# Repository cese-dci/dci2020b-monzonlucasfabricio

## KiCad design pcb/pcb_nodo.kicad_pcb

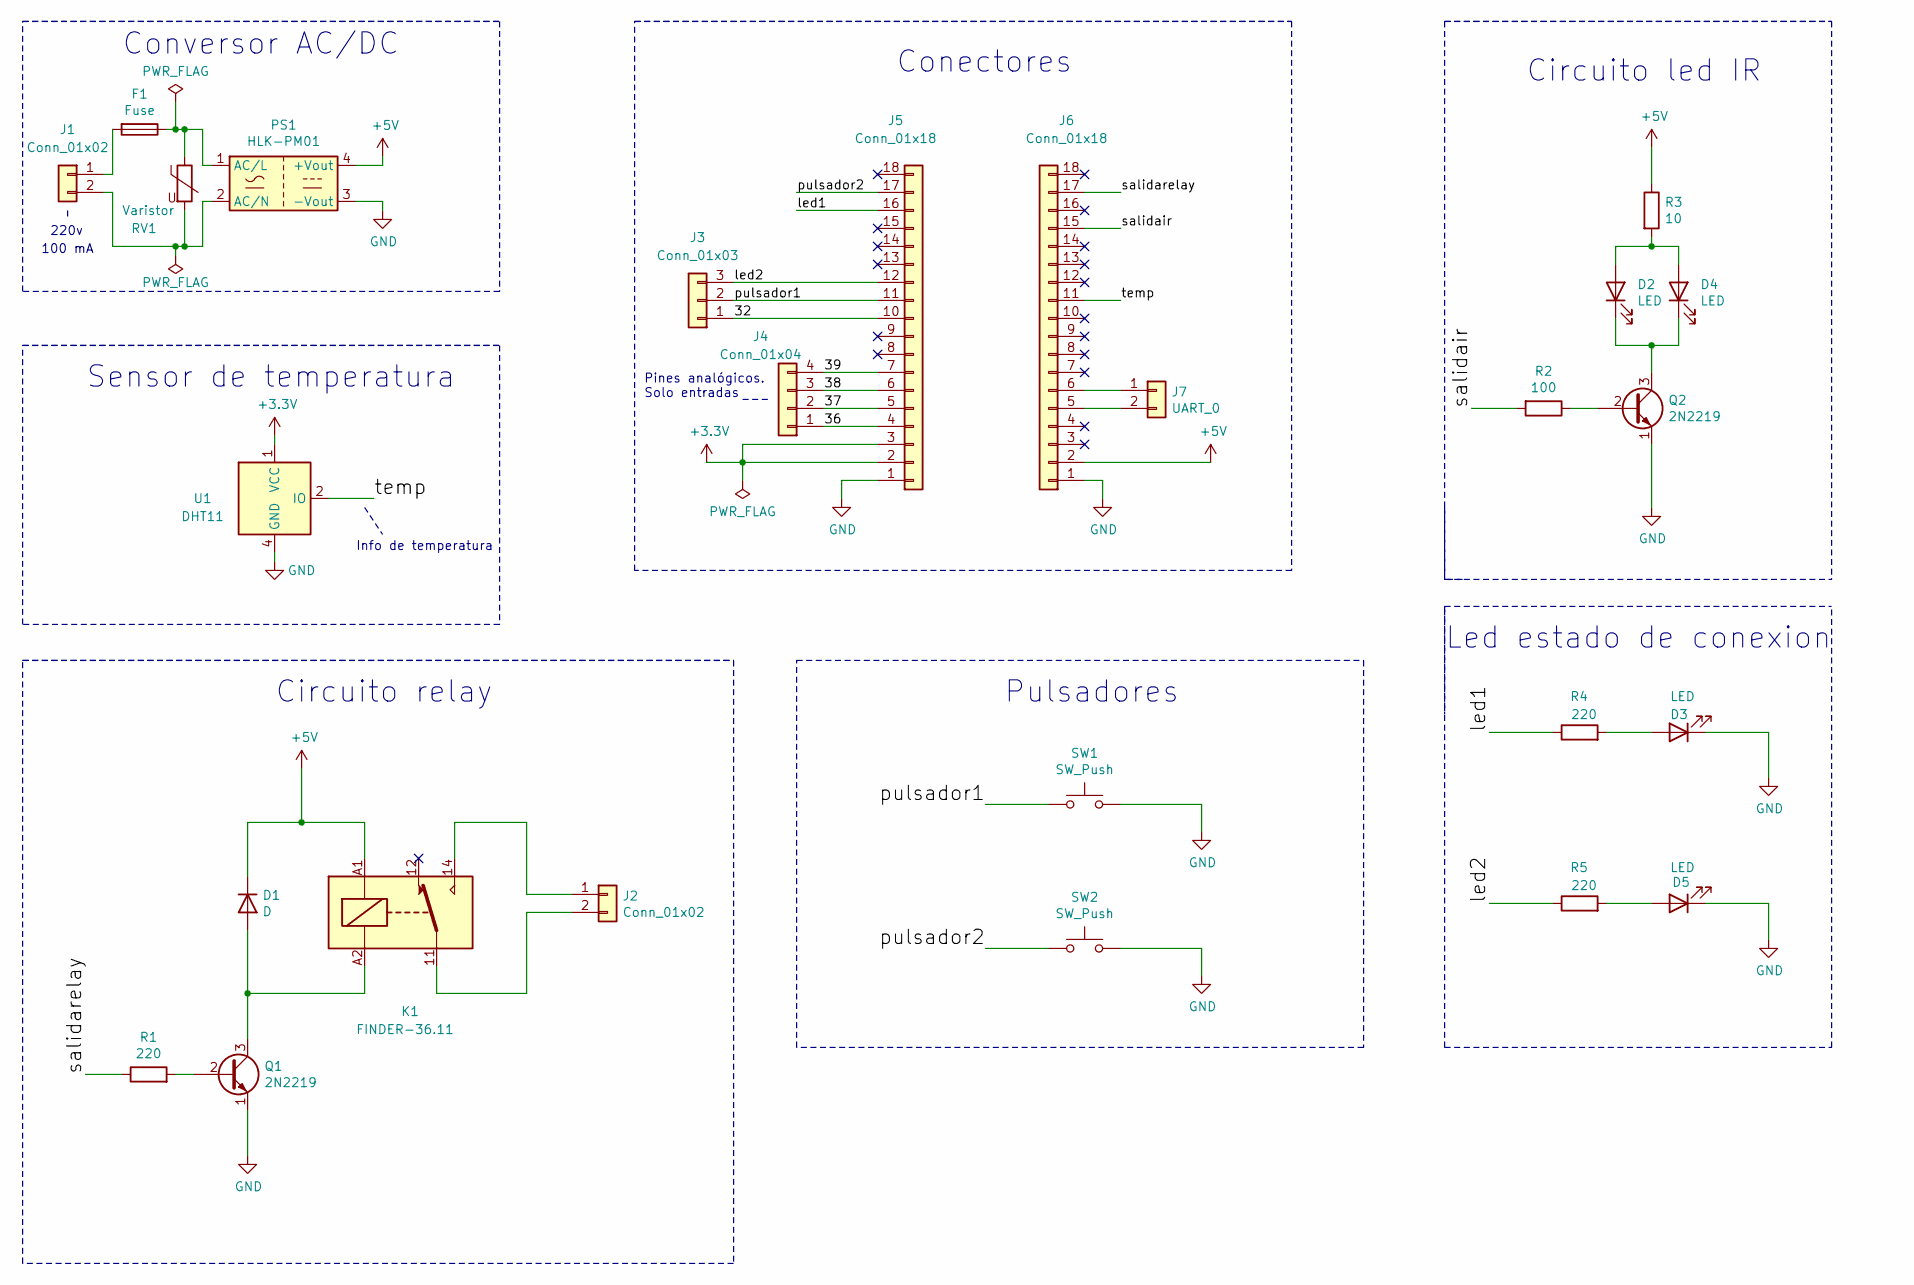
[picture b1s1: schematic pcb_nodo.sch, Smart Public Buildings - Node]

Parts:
D1: D; D_DO-41_SOD81_P7.62mm_Horizontal
D2, D4: LED; LED_D5.0mm_IRGrey
D3, D5: LED; LED_D3.0mm_FlatTop
F1: Fuse; Fuseholder_Cylinder-5x20mm_Schurter_0031_8201_Horizontal_Op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
J1, J2: Conn_01x02; TerminalBlock_bornier-2_P5.08mm
J3: Conn_01x03; PinSocket_1x03_P2.54mm_Vertical
J4: Conn_01x04; PinSocket_1x04_P2.54mm_Vertical
J5, J6: Conn_01x18; PinSocket_1x18_P2.54mm_Vertical
J7: UART_0; PinSocket_1x02_P2.54mm_Vertical
K1: FINDER-36.11; Relay_SPDT_Finder_36.11
PS1: HLK-PM01; Converter_ACDC_HiLink_HLK-PMxx
Q1, Q2: 2N2219; TO-92_Inline_Wide
R1, R4, R5: 220; R_Axial_DIN0309_L9.0mm_D3.2mm_P12.70mm_Horizontal
R2: 100; R_Axial_DIN0309_L9.0mm_D3.2mm_P12.70mm_Horizontal
R3: 10; R_Axial_DIN0309_L9.0mm_D3.2mm_P12.70mm_Horizontal
RV1: Varistor; RV_Disc_D7mm_W3.4mm_P5mm
SW1: SW_Push; TerminalBlock_bornier-2_P5.08mm
SW2: SW_Push; PinHeader_1x02_P2.54mm_Vertical
U1: DHT11; Aosong_DHT11_5.5x12.0_P2.54mm

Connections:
+3V3: J5.2, J5.3, U1.1 (VCC)
+5V: D1.1 (K), J6.2, K1.A1, PS1.4 (+Vout), R3.1
/32: J3.1, J5.10
/36: J4.1, J5.4
/37: J4.2, J5.5
/38: J4.3, J5.6
/39: J4.4, J5.7
/led1: J5.16, R4.1
/led2: J3.3, J5.12, R5.1
/pulsador1: J3.2, J5.11, SW1.1
/pulsador2: J5.17, SW2.1
/salidair: J6.15, R2.2
/salidarelay: J6.17, R1.1
/temp: J6.11, U1.2 (IO)
GND: D3.1 (K), D5.1 (K), J5.1, J6.1, PS1.3 (-Vout), Q1.1 (E), Q2.1 (E), SW1.2, SW2.2, U1.4 (GND)
unnamed: D1.2 (A), K1.A2, Q1.3 (C)
unnamed: D2.1 (K), D4.1 (K), Q2.3 (C)
unnamed: D2.2 (A), D4.2 (A), R3.2
unnamed: D3.2 (A), R4.2
unnamed: D5.2 (A), R5.2
unnamed: F1.1, PS1.1 (AC/L), RV1.1
unnamed: F1.2, J1.1
unnamed: J1.2, PS1.2 (AC/N), RV1.2
unnamed: J2.1, K1.14
unnamed: J2.2, K1.11
unnamed: J6.5, J7.2
unnamed: J6.6, J7.1
unnamed: Q1.2 (B), R1.2
unnamed: Q2.2 (B), R2.1

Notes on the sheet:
Conectores
Circuito relay
Led estado de conexion
Pulsadores
Conversor AC/DC
Circuito led IR
Pines analógicos. Solo entradas
Sensor de temperatura
Info de temperatura
220v
100 mA

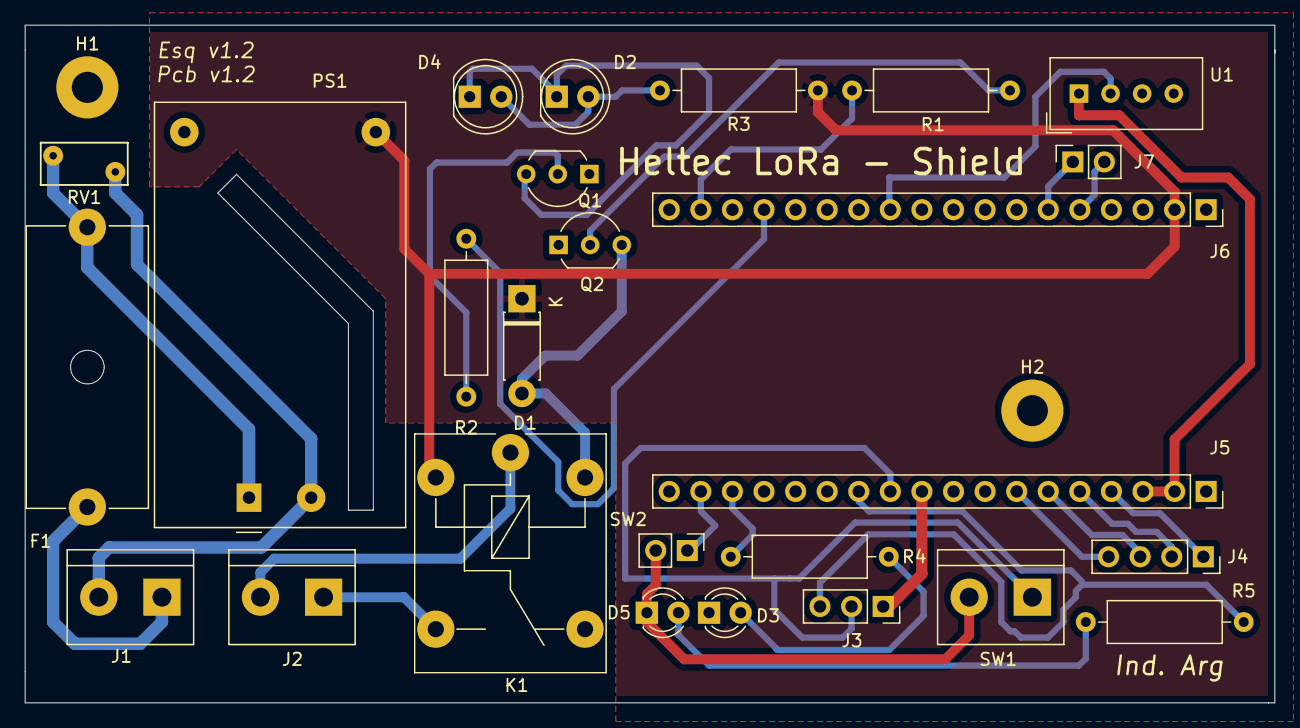
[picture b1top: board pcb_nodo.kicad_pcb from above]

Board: 2 copper layers, 100.5 x 54.5 mm, 28 parts (0 on the bottom side), 29 nets.

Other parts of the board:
H1, H2: MountingHole; MountingHole_2.5mm_Pad

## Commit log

2020-09-25 Esquematico casi listo
2020-10-05 enrutado
2020-10-14 avances
2020-10-15 para revision
2020-10-26 Para revision final

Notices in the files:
pcb/pcb_nodo.kicad_pcb:
Licencia BSD (proyecto CIAA), GPL o OHL (Cern).
